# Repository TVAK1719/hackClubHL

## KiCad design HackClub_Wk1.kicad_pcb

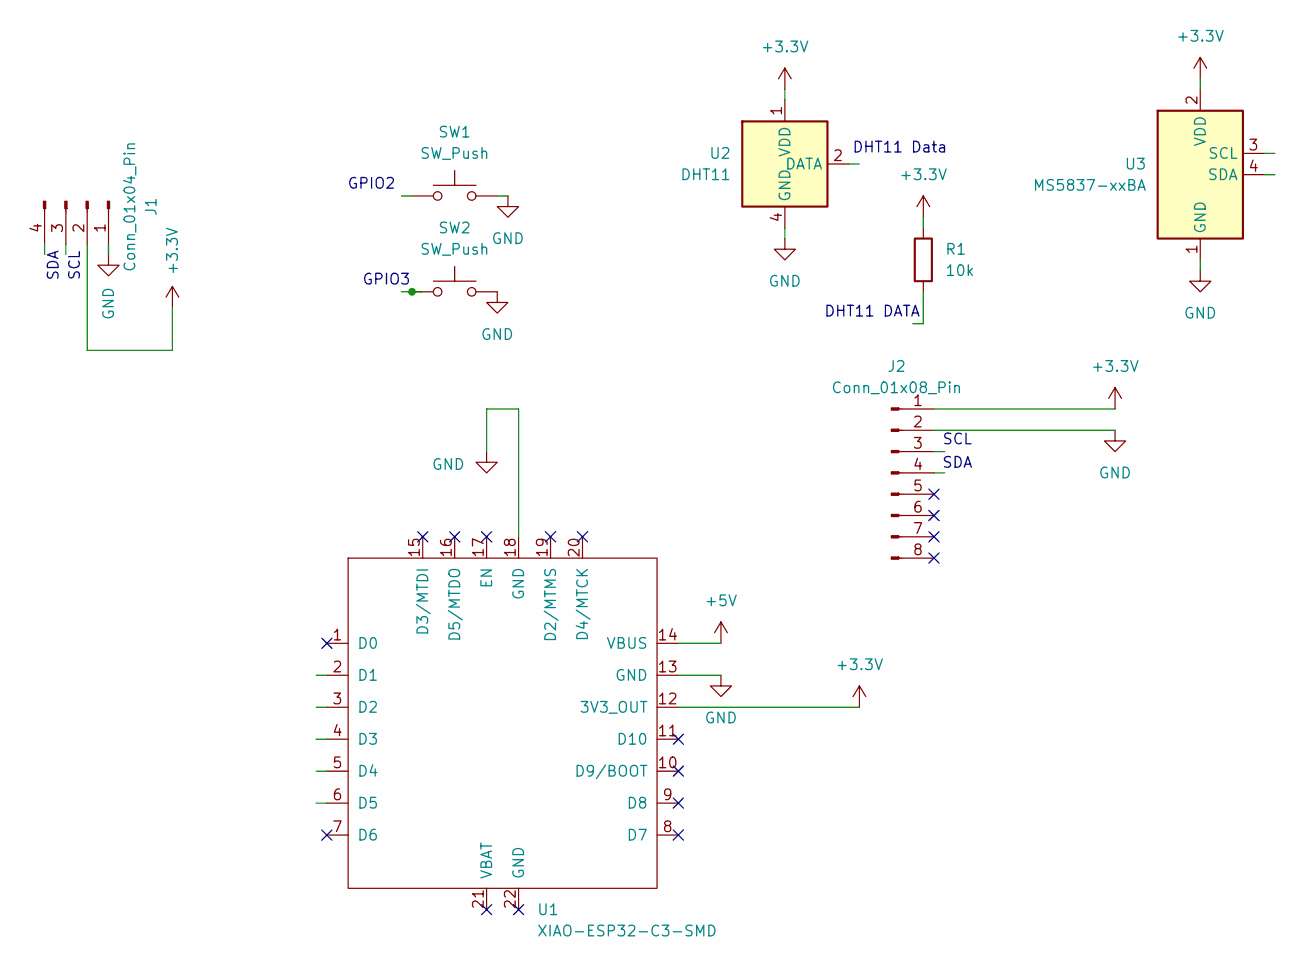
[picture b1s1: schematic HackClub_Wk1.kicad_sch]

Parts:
J1: Conn_01x04_Pin; Display_128x64_096_I2C
J2: Conn_01x08_Pin; PinHeader_1x08_P2.54mm_Vertical
R1: 10k; R_Axial_DIN0207_L6.3mm_D2.5mm_P7.62mm_Horizontal
SW1, SW2: SW_Push; SW_Cherry_MX_1.00u_PCB
U1: XIAO-ESP32-C3-SMD
U2: DHT11; Aosong_DHT11_5.5x12.0_P2.54mm
U3: MS5837-xxBA; TE_MS5837-xxBA

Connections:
+3.3V: J1.2, J2.1, R1.1, U1.12 (3V3_OUT), U2.1 (VDD), U3.2 (VDD)
+5V: U1.14 (VBUS)
GND: J1.1, J2.2, SW1.2 (2_2), SW2.2 (2_2), U1.13 (GND), U1.18 (GND), U2.4 (GND), U3.1 (GND)

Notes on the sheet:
SCL
GPIO3
DHT11 DATA
SDA
GPIO2
DHT11 Data

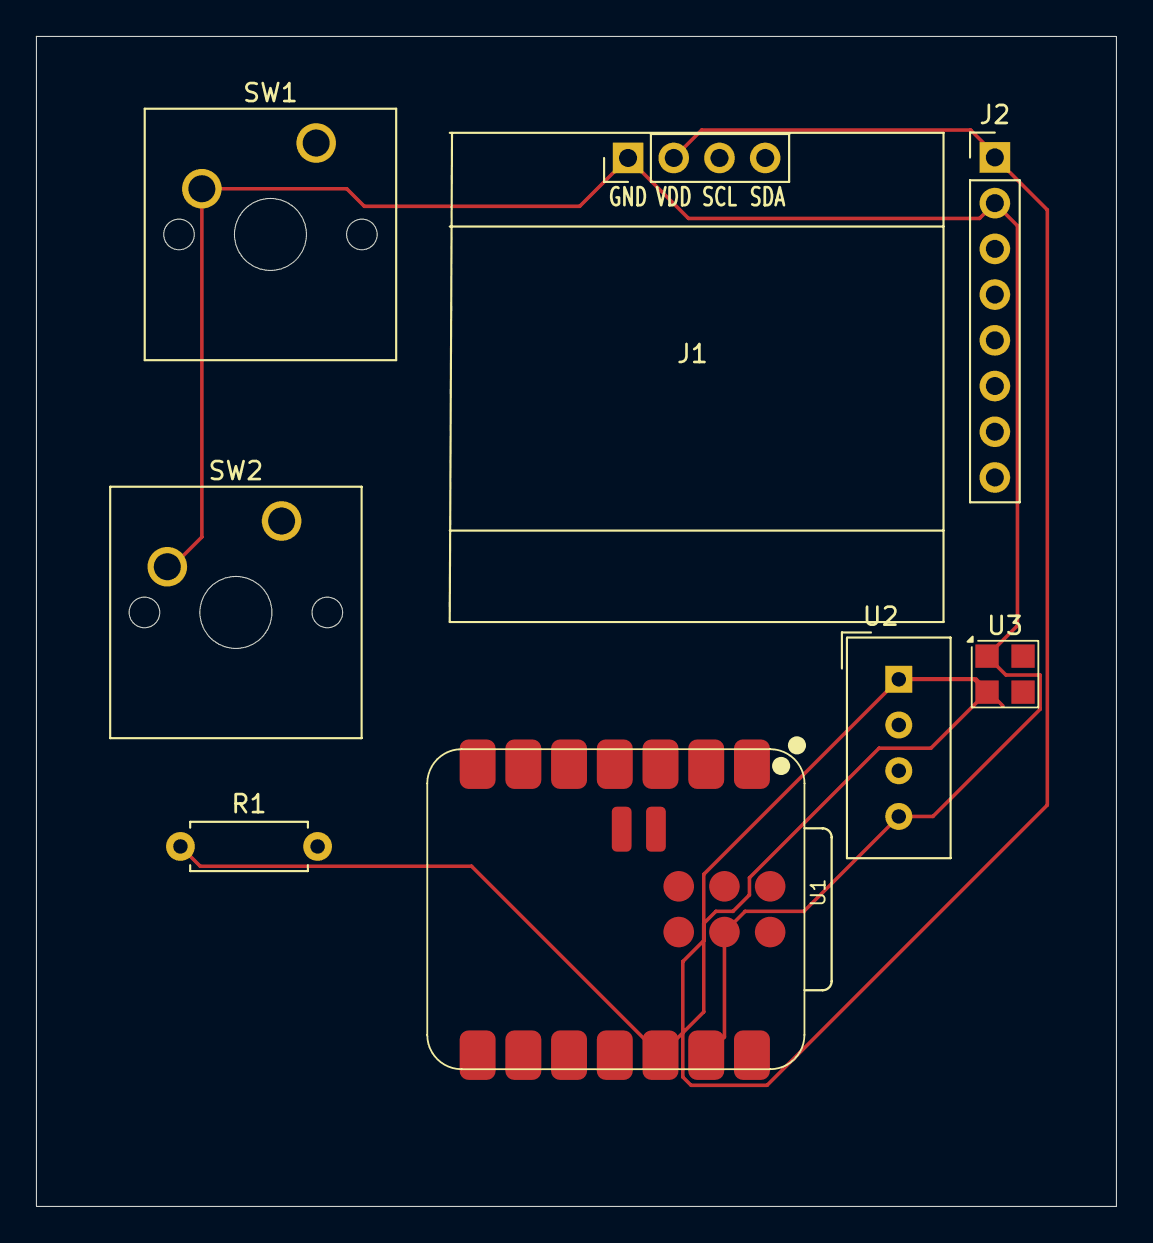
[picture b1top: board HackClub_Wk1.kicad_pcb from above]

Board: 2 copper layers, 60.0 x 65.0 mm, 8 parts (0 on the bottom side), 2 nets.
